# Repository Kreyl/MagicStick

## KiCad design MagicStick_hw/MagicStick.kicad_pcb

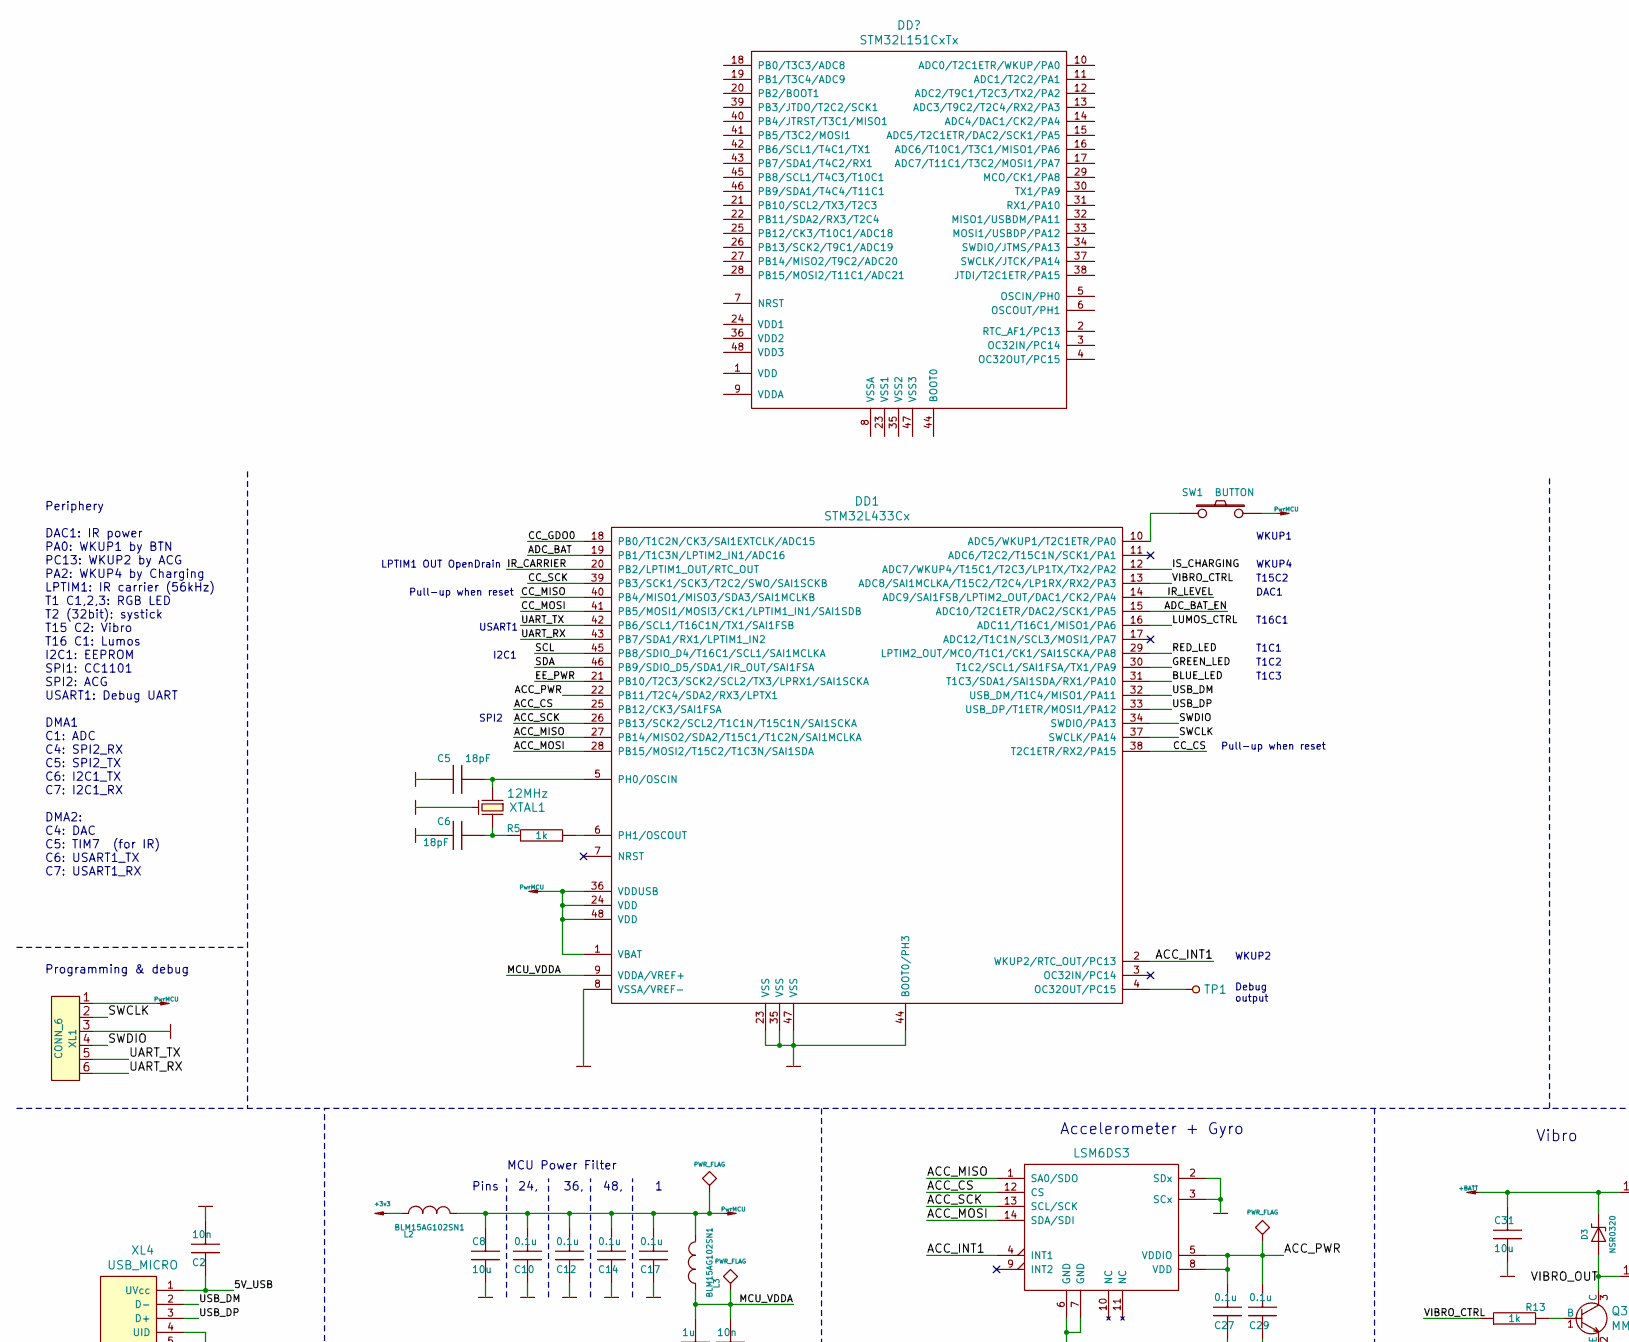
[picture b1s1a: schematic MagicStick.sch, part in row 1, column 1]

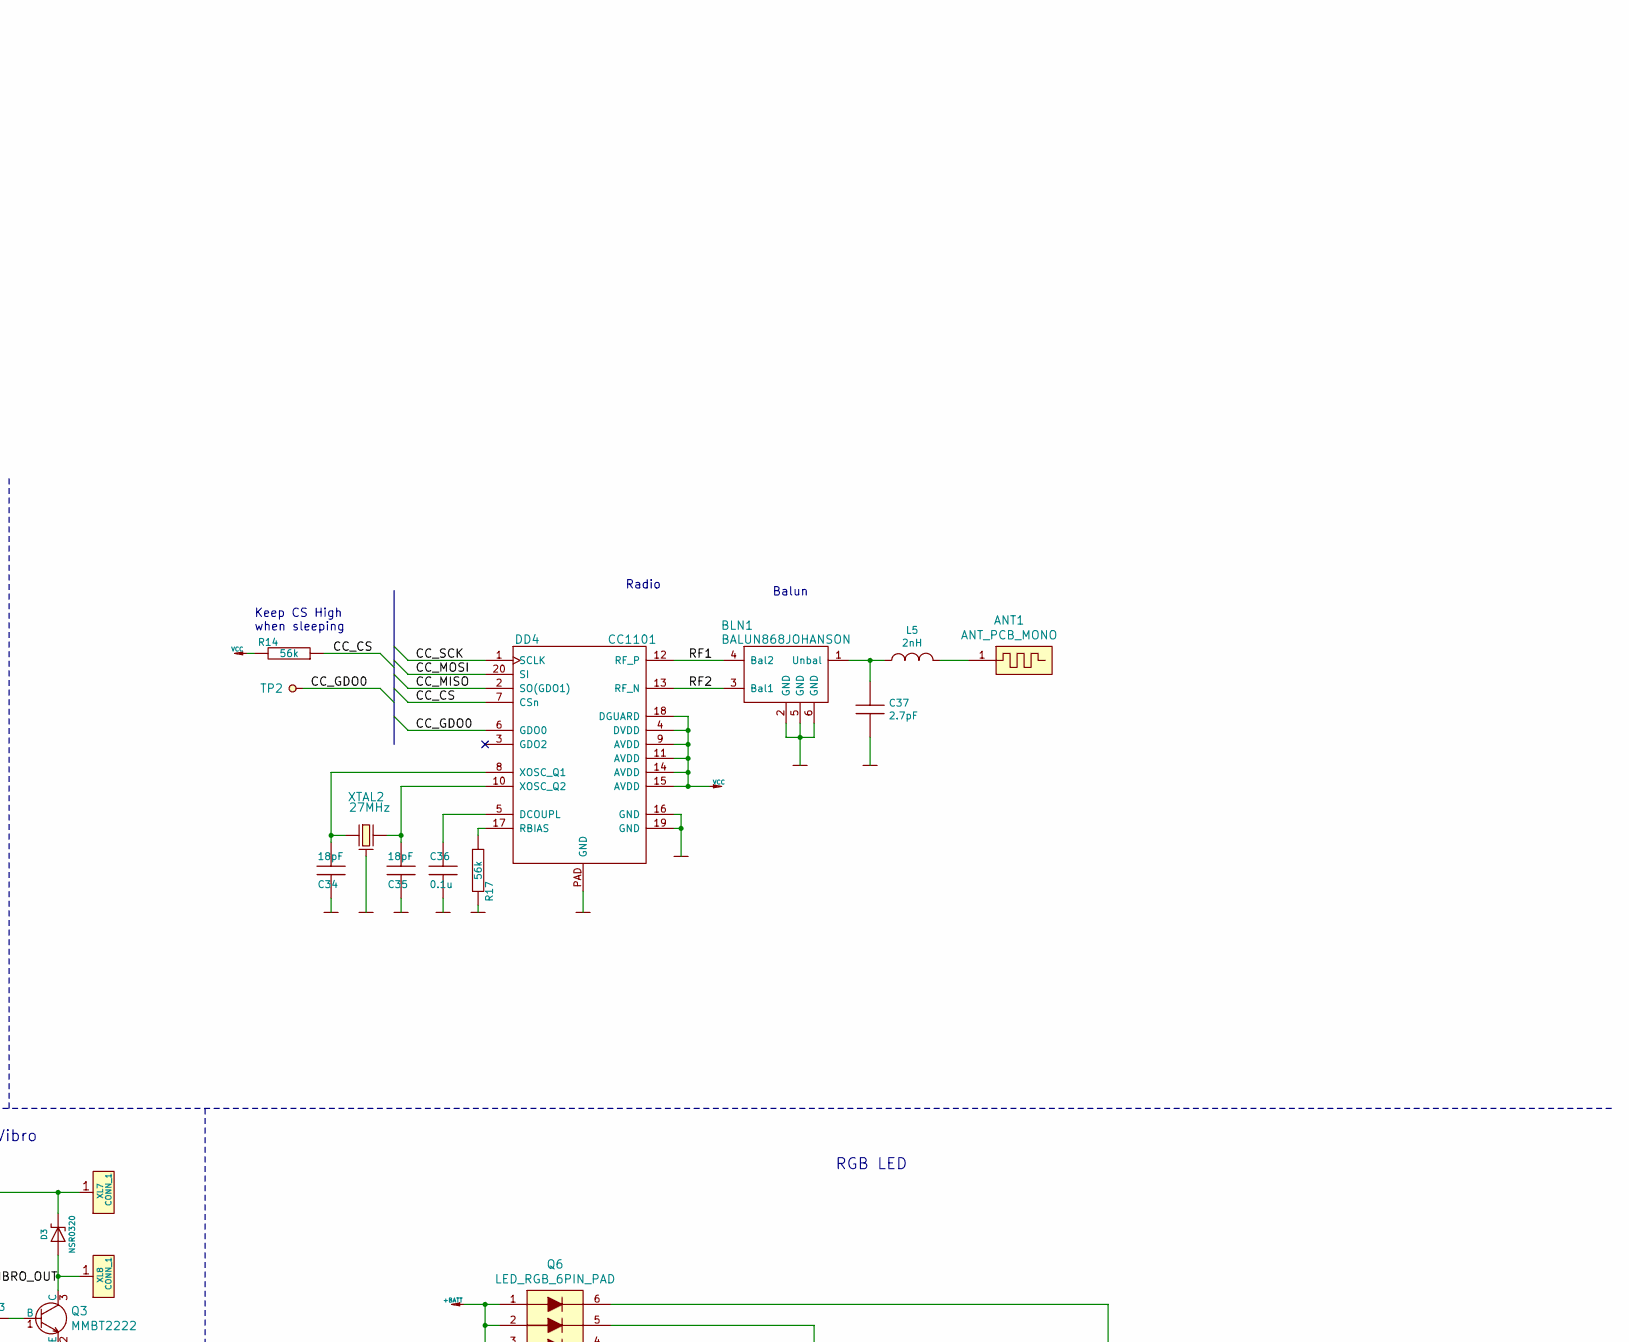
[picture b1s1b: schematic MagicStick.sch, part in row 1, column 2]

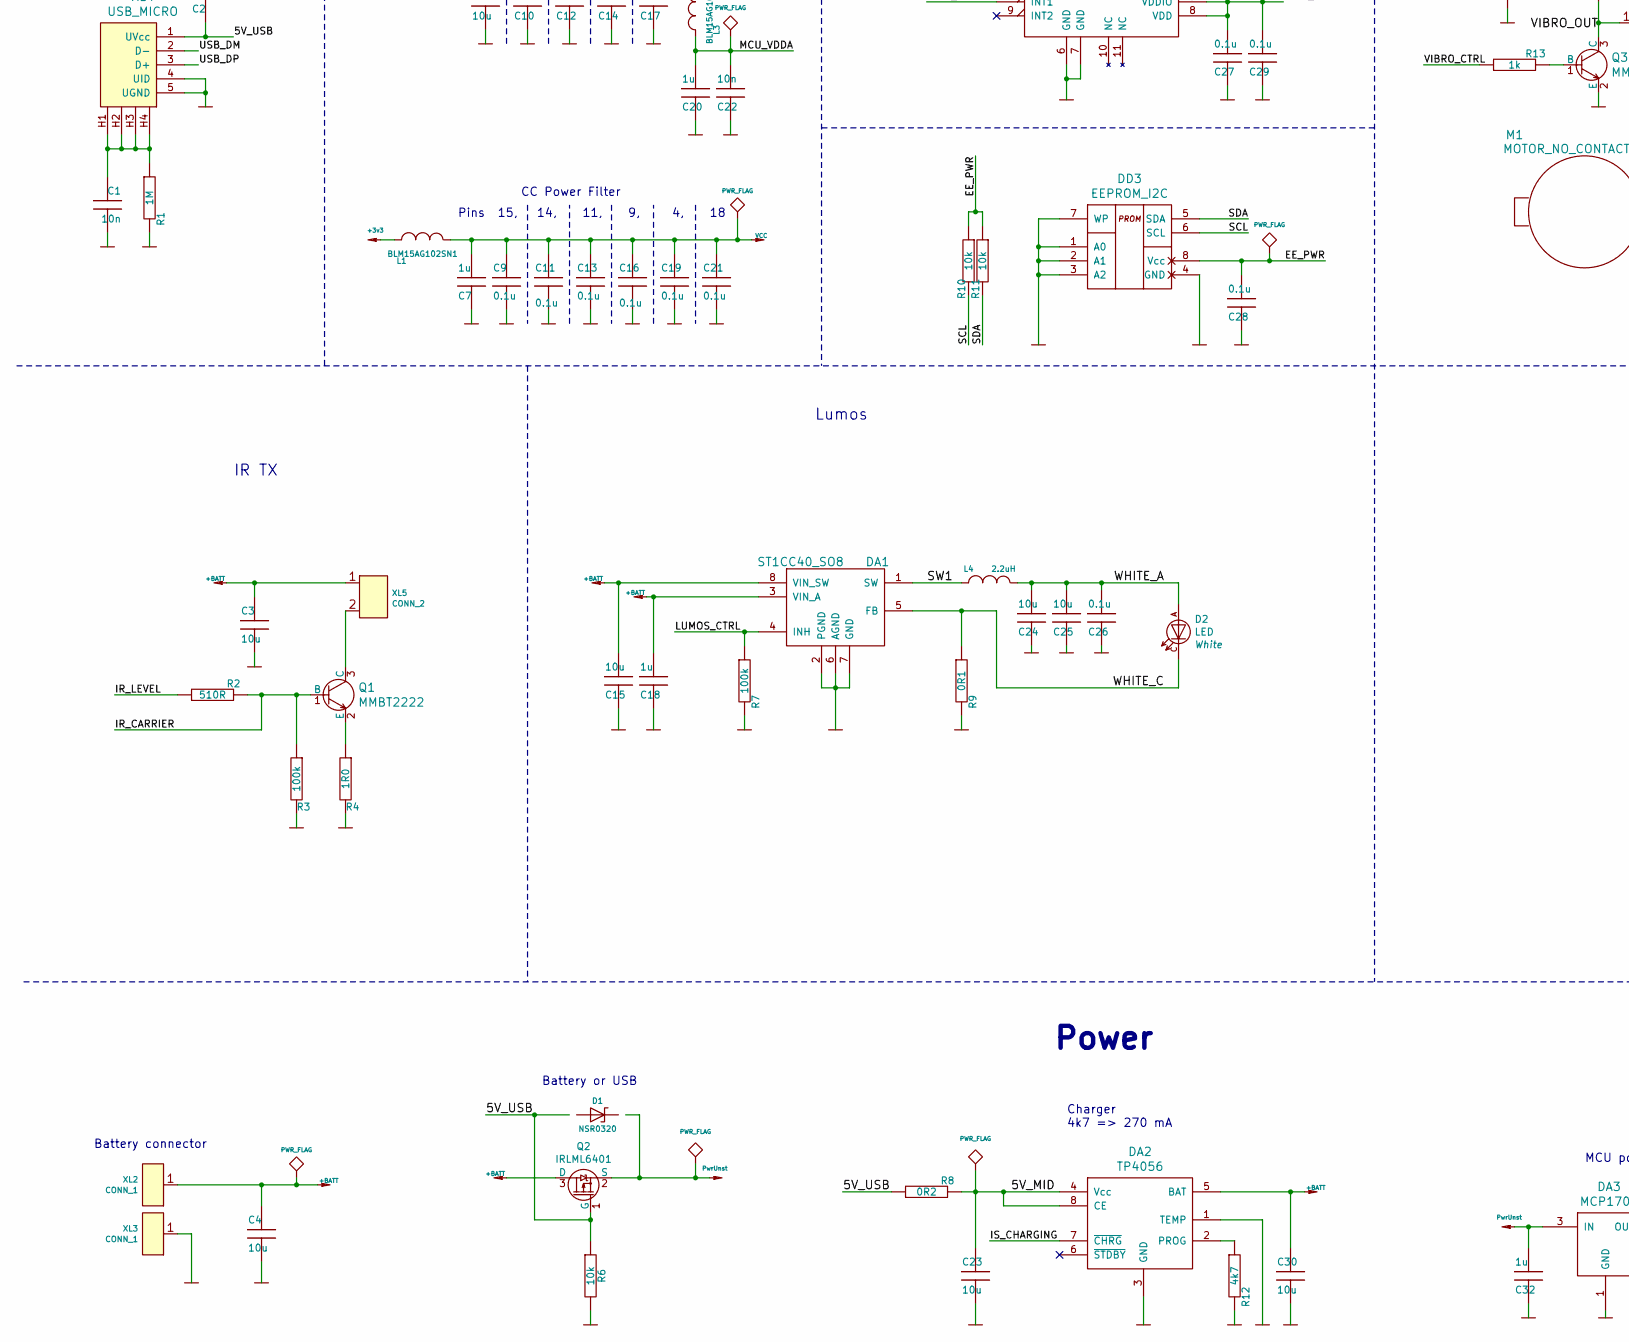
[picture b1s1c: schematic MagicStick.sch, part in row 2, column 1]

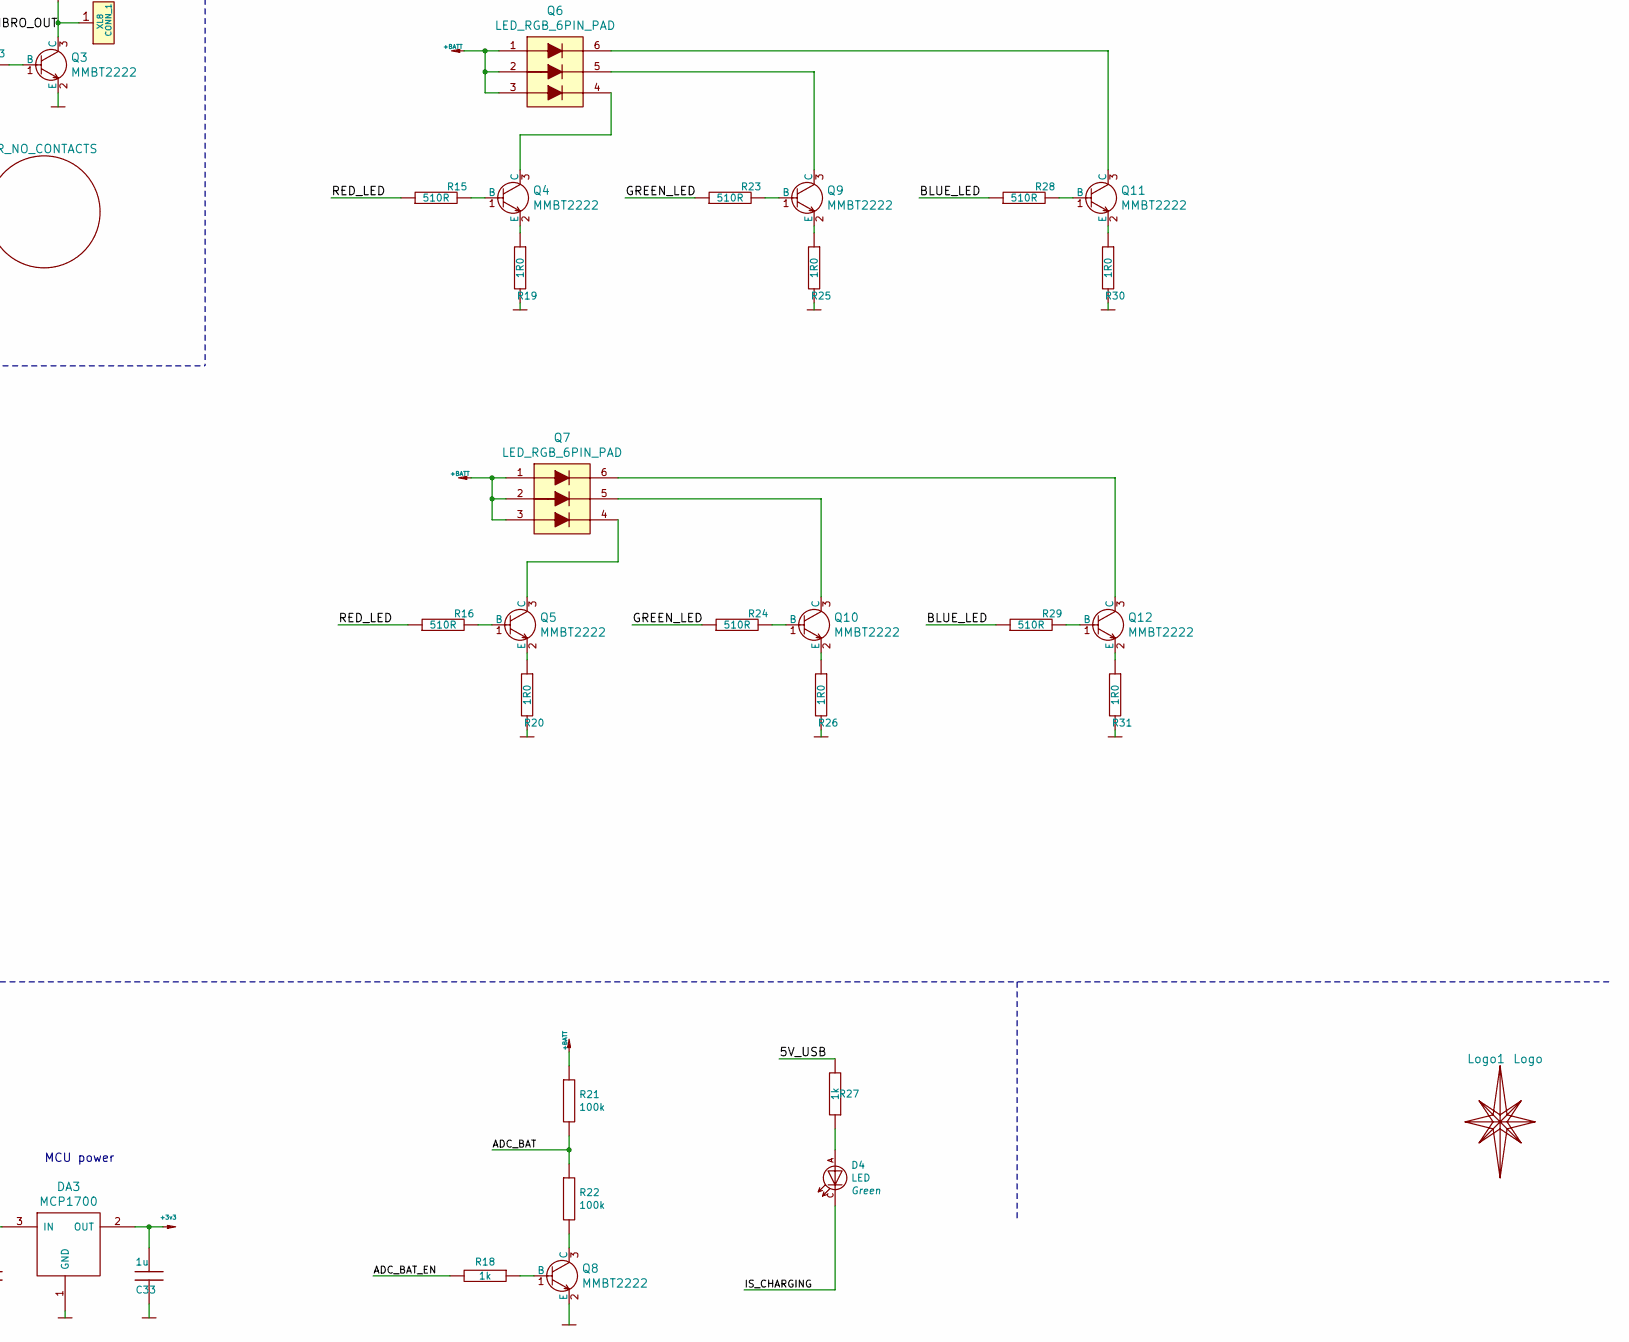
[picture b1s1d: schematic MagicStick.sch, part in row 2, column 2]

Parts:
ANT1: ANT_PCB_MONO; MagicStick
BLN1: BALUN868JOHANSON; BALUN_JOHANSON868
C1, C2, C22: 10n; CAP_0603
C3, C4, C8, C15, C23, C24, C25, C30, C31: 10u; CAP_0603
C5, C6, C34, C35: 18pF; CAP_0603
C7, C18, C20, C32, C33: 1u; CAP_0603
C9, C10, C11, C12, C13, C14, C16, C17, C19, C21, C26, C27, C28, C29, C36: 0.1u; CAP_0603
C37: 2.7pF; CAP_0402
D1, D3: NSR0320; SOD323
D2: LED; Cree_J3030
D4: LED; LED_0603
DA1: ST1CC40_SO8; SO8_150MIL
DA2: TP4056; SO8_150MIL
DA3: MCP1700; SOT23-3A
DD1: STM32L433Cx; LQFP48
DD2: LSM6DS3; 14_3x2d5_p0d5
DD3: EEPROM_I2C; SO8_150MIL
DD4: CC1101; QFN20
L1, L2, L3: BLM15AG102SN1; IND_0402
L4: 2.2uH; IND_SRN2512
L5: 2nH; IND_0402
Logo1: Logo; Ostranna_8x8
M1: MOTOR_NO_CONTACTS; Motor_no_Contacts
Q1, Q3, Q4, Q5, Q8, Q9, Q10, Q11, Q12: MMBT2222; SOT23-3
Q2: IRLML6401; SOT23-3
Q6, Q7: LED_RGB_6PIN_PAD; EpistarRGB
R1: 1M; RES_0603
R2, R15, R16, R23, R24, R28, R29: 510R; RES_0603
R3, R7, R21, R22: 100k; RES_0603
R4, R19, R20, R25, R26, R30, R31: 1R0; RES_0805
R5, R13, R18, R27: 1k; RES_0603
R6, R10, R11: 10k; RES_0603
R8: 0R2; RES_1206
R9: 0R1; RES_1206
R12: 4k7; RES_0603
R14, R17: 56k; RES_0603
SW1: BUTTON; BTN_4x4_SMD
TP1, TP2: TESTPOINT; TESTPOINT_1MM
XL1: CONN_6; PLS-6-NoHole
XL2, XL3, XL7, XL8: CONN_1; Oval3x1.5
XL4: USB_MICRO; USBmicro_MOLEX_1050170001
XL5: CONN_2; PBS-2
XTAL1: 12MHz; 03225C4
XTAL2: 27MHz; 03225C4

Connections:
+3.3V: C33.1, DA3.2 (OUT), L1.2, L2.2
+BATT: C3.2, C4.2, C15.1, C18.1, C30.2, C31.2, D3.C, DA1.3 (VIN_A), DA1.8 (VIN_SW), DA2.5 (BAT), Q2.3 (D), Q6.1, Q6.2, Q6.3, Q7.1, Q7.2, Q7.3, R21.1, XL2.1, XL5.1, XL7.1
/5V_MID: C23.2, DA2.4 (Vcc), DA2.8 (CE), R8.2
/5V_USB: C2.2, D1.A, Q2.1 (G), R6.1, R8.1, R27.2, XL4.1 (UVcc)
/ACC_CS: DD1.25 (PB12/CK3/SAI1FSA), DD2.12 (CS)
/ACC_INT1: DD1.2 (WKUP2/RTC_OUT/PC13), DD2.4 (INT1)
/ACC_MISO: DD1.27 (PB14/MISO2/SDA2/T15C1/T1C2N/SAI1MCLKA), DD2.1 (SA0/SDO)
/ACC_MOSI: DD1.28 (PB15/MOSI2/T15C2/T1C3N/SAI1SDA), DD2.14 (SDA/SDI)
/ACC_PWR: C27.1, C29.1, DD1.22 (PB11/T2C4/SDA2/RX3/LPTX1), DD2.5 (VDDIO), DD2.8 (VDD)
/ACC_SCK: DD1.26 (PB13/SCK2/SCL2/T1C1N/T15C1N/SAI1SCKA), DD2.13 (SCL/SCK)
/ADC_BAT: DD1.19 (PB1/T1C3N/LPTIM2_IN1/ADC16), R21.2, R22.1
/ADC_BAT_EN: DD1.15 (ADC10/T2C1ETR/DAC2/SCK1/PA5), R18.2
/BLUE_LED: DD1.31 (T1C3/SDA1/SAI1SDA/RX1/PA10), R28.1, R29.1
/CC_CS: DD1.38 (T2C1ETR/RX2/PA15), DD4.7 (CSn), R14.1
/CC_GDO0: DD1.18 (PB0/T1C2N/CK3/SAI1EXTCLK/ADC15), DD4.6 (GDO0), TP2.1
/CC_MISO: DD1.40 (PB4/MISO1/MISO3/SDA3/SAI1MCLKB), DD4.2 (SO(GDO1))
/CC_MOSI: DD1.41 (PB5/MOSI1/MOSI3/CK1/LPTIM1_IN1/SAI1SDB), DD4.20 (SI)
/CC_SCK: DD1.39 (PB3/SCK1/SCK3/T2C2/SWO/SAI1SCKB), DD4.1 (SCLK)
/EE_PWR: C28.1, DD1.21 (PB10/T2C3/SCK2/SCL2/TX3/LPRX1/SAI1SCKA), DD3.8 (Vcc), R10.1, R11.1
/GREEN_LED: DD1.30 (T1C2/SCL1/SAI1FSA/TX1/PA9), R23.1, R24.1
/IR_CARRIER: DD1.20 (PB2/LPTIM1_OUT/RTC_OUT), Q1.1 (B), R2.2, R3.1
/IR_LEVEL: DD1.14 (ADC9/SAI1FSB/LPTIM2_OUT/DAC1/CK2/PA4), R2.1
/IS_CHARGING: D4.C, DA2.7 (~CHRG), DD1.12 (ADC7/WKUP4/T15C1/T2C3/LP1TX/TX2/PA2)
/LUMOS_CTRL: DA1.4 (INH), DD1.16 (ADC11/T16C1/MISO1/PA6), R7.1
/MCU_VDDA: C20.1, C22.1, DD1.9 (VDDA/VREF+), L3.2
/RED_LED: DD1.29 (LPTIM2_OUT/MCO/T1C1/CK1/SAI1SCKA/PA8), R15.1, R16.1
/RF1: BLN1.4 (Bal2), DD4.12 (RF_P)
/RF2: BLN1.3 (Bal1), DD4.13 (RF_N)
/SCL: DD1.45 (PB8/SDIO_D4/T16C1/SCL1/SAI1MCLKA), DD3.6 (SCL), R10.2
/SDA: DD1.46 (PB9/SDIO_D5/SDA1/IR_OUT/SAI1FSA), DD3.5 (SDA), R11.2
/SW1: DA1.1 (SW), L4.2
/SWCLK: DD1.37 (SWCLK/PA14), XL1.2
/SWDIO: DD1.34 (SWDIO/PA13), XL1.4
/UART_RX: DD1.43 (PB7/SDA1/RX1/LPTIM1_IN2), XL1.6
/UART_TX: DD1.42 (PB6/SCL1/T16C1N/TX1/SAI1FSB), XL1.5
/USB_DM: DD1.32 (USB_DM/T1C4/MISO1/PA11), XL4.2 (D-)
/USB_DP: DD1.33 (USB_DP/T1ETR/MOSI1/PA12), XL4.3 (D+)
/VIBRO_CTRL: DD1.13 (ADC8/SAI1MCLKA/T15C2/T2C4/LP1RX/RX2/PA3), R13.1
/VIBRO_OUT: D3.A, Q3.3 (C), XL8.1
/WHITE_A: C24.1, C25.1, C26.1, D2.A, L4.1
/WHITE_C: D2.C, DA1.5 (FB), R9.1
GND: BLN1.2 (GND), BLN1.5 (GND), BLN1.6 (GND), C1.1, C2.1, C3.1, C4.1, C5.2, C6.2, C7.2, C8.1, C9.2, C10.2, C11.2, C12.2, C13.2, C14.2, C15.2, C16.2, C17.2, C18.2, C19.2, C20.2, C21.2, C22.2, C23.1, C24.2, C25.2, C26.2, C27.2, C28.2, C29.2, C30.1, C31.1, C32.2, C33.2, C34.2, C35.2, C36.1, C37.2, DA1.2 (PGND), DA1.6 (AGND), DA1.7 (GND), DA2.1 (TEMP), DA2.3 (GND), DA3.1 (GND), DD1.8 (VSSA/VREF-), DD1.23 (VSS), DD1.35 (VSS), DD1.44 (BOOT0/PH3), DD1.47 (VSS), DD2.2 (SDx), DD2.3 (SCx), DD2.6 (GND), DD2.7 (GND), DD3.1 (A0), DD3.2 (A1), DD3.3 (A2), DD3.4 (GND), DD3.7 (WP), DD4.16 (GND), DD4.19 (GND), DD4.PAD (GND), Q3.2 (E), Q8.2 (E), R1.2, R3.2, R4.2, R6.2, R7.2, R9.2, R12.2, R17.2, R19.2, R20.2, R25.2, R26.2, R30.2, R31.2, XL1.3, XL3.1, XL4.4 (UID), XL4.5 (UGND), XTAL1.H, XTAL2.H; also elsewhere on the board
unnamed 42: ANT1.1, L5.2; also elsewhere on the board
unnamed: BLN1.1 (Unbal), C37.1, L5.1
unnamed: C1.2, R1.1, XL4.H1, XL4.H2, XL4.H3, XL4.H4
unnamed: C5.1, DD1.5 (PH0/OSCIN), XTAL1.1
unnamed: C6.1, R5.2, XTAL1.2
unnamed: C34.1, DD4.8 (XOSC_Q1), XTAL2.1
unnamed: C35.1, DD4.10 (XOSC_Q2), XTAL2.2
unnamed: C36.2, DD4.5 (DCOUPL)
unnamed: D4.A, R27.1
unnamed: DA2.2 (PROG), R12.1
unnamed: DD1.4 (OC32OUT/PC15), TP1.1
unnamed: DD1.6 (PH1/OSCOUT), R5.1
unnamed: DD1.10 (ADC5/WKUP1/T2C1ETR/PA0), SW1.1
unnamed: DD4.17 (RBIAS), R17.1
unnamed: Q1.2 (E), R4.1
unnamed: Q1.3 (C), XL5.2 (PM)
unnamed: Q3.1 (B), R13.2
unnamed: Q4.1 (B), R15.2
unnamed: Q4.2 (E), R19.1
unnamed: Q4.3 (C), Q6.4 (B)
unnamed: Q5.1 (B), R16.2
unnamed: Q5.2 (E), R20.1
unnamed: Q5.3 (C), Q7.4 (B)
unnamed: Q6.5 (G), Q9.3 (C)
unnamed: Q8.1 (B), R18.1
unnamed: Q8.3 (C), R22.2
unnamed: Q9.1 (B), R23.2
unnamed: Q9.2 (E), R25.1
unnamed: Q10.1 (B), R24.2
unnamed: Q10.2 (E), R26.1
unnamed: Q7.5 (G), Q10.3 (C)
unnamed: Q11.1 (B), R28.2
unnamed: Q11.2 (E), R30.1
unnamed: Q6.6, Q11.3 (C)
unnamed: Q12.1 (B), R29.2
unnamed: Q12.2 (E), R31.1
unnamed: Q7.6, Q12.3 (C)
PwrMCU: C8.2, C10.1, C12.1, C14.1, C17.1, DD1.1 (VBAT), DD1.24 (VDD), DD1.36 (VDDUSB), DD1.48 (VDD), L2.1, L3.1, SW1.2, XL1.1
PwrUnst: C32.1, D1.C, DA3.3 (IN), Q2.2 (S)
VCC: C7.1, C9.1, C11.1, C13.1, C16.1, C19.1, C21.1, DD4.4 (DVDD), DD4.9 (AVDD), DD4.11 (AVDD), DD4.14 (AVDD), DD4.15 (AVDD), DD4.18 (DGUARD), L1.1, R14.2

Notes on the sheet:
RGB LED
MCU Power Filter
Pins 24, 36, 48, 1
CC Power Filter
Pins 15, 14, 11, 9, 4, 18
Periphery DAC1: IR power PA0: WKUP1 by BTN PC13: WKUP2 by ACG PA2: WKUP4 by Charging LPTIM1: IR carrier (56kHz) T1 C1,2,3: RGB LED T2 (32bit): systick T15 C2: Vibro T16 C1: Lumos I2C1: EEPROM SPI1: CC1101 SPI2: ACG USART1: Debug UART DMA1 C1: ADC C4: SPI2_RX C5: SPI2_TX C6: I2C1_TX C7: I2C1_RX DMA2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
Programming & debug
Radio
Balun
Keep CS High when sleeping
Accelerometer + Gyro
MCU power
Power
Charger 4k7 => 270 mA
Battery or USB
Battery connector
Vibro
WKUP2
T1C1
T1C2
T1C3
I2C1
SPI2
LPTIM1 OUT OpenDrain
Pull-up when reset
Debug output
USART1
IR TX
Lumos
T16C1
T15C2
DAC1
WKUP1
WKUP4

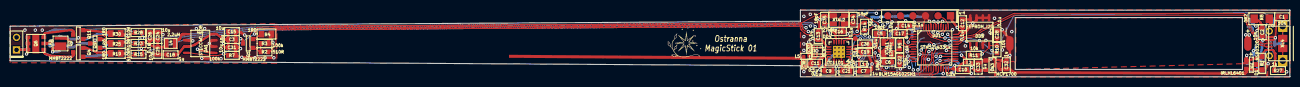
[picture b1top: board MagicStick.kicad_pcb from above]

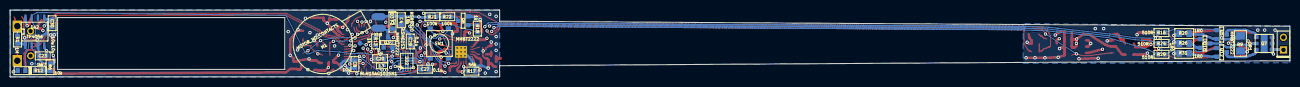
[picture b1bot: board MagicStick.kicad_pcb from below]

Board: 4 copper layers, 259.1 x 13.5 mm, 113 parts (38 on the bottom side), 82 nets.

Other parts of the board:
C38: *; CAP_0402

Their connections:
GND: C38.2; also elsewhere on the board
unnamed 42: C38.1; also elsewhere on the board

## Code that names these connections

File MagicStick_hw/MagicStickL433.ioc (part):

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Mcu.Name=STM32L433C(B-C)Tx
Mcu.Package=LQFP48
Mcu.UserName=STM32L433CBTx
PA0.Mode=SYS_WakeUp0
PA0.Signal=SYS_WKUP1
PA1.Mode=PWM Generation1 CH1N
PA1.Signal=TIM15_CH1N
PA10.Signal=S_TIM1_CH3
PA11.Mode=Device
PA11.Signal=USB_DM
PA12.Mode=Device
PA12.Signal=USB_DP
PA13\ (JTMS-SWDIO).Mode=Serial_Wire
PA13\ (JTMS-SWDIO).Signal=SYS_JTMS-SWDIO
PA14\ (JTCK-SWCLK).Mode=Serial_Wire
PA14\ (JTCK-SWCLK).Signal=SYS_JTCK-SWCLK
PA15\ (JTDI).Signal=GPIO_Output
PA2.Mode=SYS_WakeUp3
PA2.Signal=SYS_WKUP4
PA3.Signal=S_TIM15_CH2
PA4.Signal=COMP_DAC11_group
PA5.Signal=GPIO_Output
PA6.Signal=S_TIM16_CH1
PA8.Signal=S_TIM1_CH1
PA9.Signal=S_TIM1_CH2
PB0.Signal=GPIO_Input
PB1.Signal=ADCx_IN16
PB10.Signal=GPIO_Output
PB11.Signal=GPIO_Output
PB12.Signal=GPIO_Output
PB13.Mode=Full_Duplex_Master
PB13.Signal=SPI2_SCK
PB14.Mode=Full_Duplex_Master
PB14.Signal=SPI2_MISO
PB15.Mode=Full_Duplex_Master
PB15.Signal=SPI2_MOSI
PB2.Mode=WaveformGeneration
PB2.Signal=LPTIM1_OUT
PB3\ (JTDO-TRACESWO).Mode=Full_Duplex_Master
PB3\ (JTDO-TRACESWO).Signal=SPI1_SCK
PB4\ (NJTRST).Mode=Full_Duplex_Master
PB4\ (NJTRST).Signal=SPI1_MISO
PB5.Mode=Full_Duplex_Master
PB5.Signal=SPI1_MOSI
PB6.Mode=Asynchronous
PB6.Signal=USART1_TX
PB7.Mode=Asynchronous
PB7.Signal=USART1_RX
PB8.Mode=I2C
PB8.Signal=I2C1_SCL
PB9.Mode=I2C
PB9.Signal=I2C1_SDA
PC13.Mode=SYS_WakeUp1
PC13.Signal=SYS_WKUP2
PC15-OSC32_OUT\ (PC15).Signal=GPIO_Output
PH0-OSC_IN\ (PH0).Mode=HSE-External-Oscillator
PH0-OSC_IN\ (PH0).Signal=RCC_OSC_IN
PH1-OSC_OUT\ (PH1).Mode=HSE-External-Oscillator
PH1-OSC_OUT\ (PH1).Signal=RCC_OSC_OUT
RCC.HSE_VALUE=12000000
RCC.SYSCLKFreq_VALUE=16000000
RCC.SYSCLKSource=RCC_SYSCLKSOURCE_PLLCLK
board=custom

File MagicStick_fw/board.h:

#pragma once

// ==== General ====
#define APP_NAME            "MagicStick"

// Version of PCB
#define PCB_VER                 1

// MCU type as defined in the ST header.
#define STM32L433xx

// Freq of external crystal if any. Leave it here even if not used.
#define CRYSTAL_FREQ_HZ         12000000

// OS timer settings
#define STM32_ST_IRQ_PRIORITY   2
#define STM32_ST_USE_TIMER      2
#define SYS_TIM_CLK             (Clk.APB1FreqHz)    // Timer 5 is clocked by APB1

//  Periphery
#define I2C1_ENABLED            TRUE
#define I2C2_ENABLED            FALSE
#define I2C3_ENABLED            FALSE
#define SIMPLESENSORS_ENABLED   TRUE
#define BUTTONS_ENABLED         TRUE

#define ADC_REQUIRED            FALSE
#define STM32_DMA_REQUIRED      TRUE    // Leave this macro name for OS

#if 1 // ========================== GPIO =======================================
// EXTI
#define INDIVIDUAL_EXTI_IRQ_REQUIRED    FALSE

// Buttons
#define BTN1_PIN        GPIOA, 0

// Vibro
#define VIBRO_CTRL      { GPIOA, 3, TIM15, 2, invNotInverted, omPushPull, 99 }

// IR TX
#define IR_LVL_PIN      GPIOA, 4
#define IR_CARRIER_PIN  GPIOB, 2

// Battery
#define IS_CHARGING     GPIOA, 2, pudPullUp
#define BAT_MEAS_EN     GPIOA, 5
#define BAT_ADC_PIN     GPIOB, 1

// Light
#define LUMOS_CTRL      { GPIOA, 6, TIM16, 1, invNotInverted, omPushPull, 255 }
#define LED_B_PIN       { GPIOA, 8, TIM1, 1, invNotInverted, omPushPull, 255 }
#define LED_R_PIN       { GPIOA, 9, TIM1, 2, invNotInverted, omPushPull, 255 }
#define LED_G_PIN       { GPIOA, 10, TIM1, 3, invNotInverted, omPushPull, 255 }

// USB
#define USB_DM          GPIOA, 11
#define USB_DP          GPIOA, 12
#define USB_AF          AF10
#define USB_DETECT_PIN  GPIOA, 7

// Radio: SPI, PGpio, Sck, Miso, Mosi, Cs, Gdo0
#define CC_Setup0       SPI1, GPIOB, 3,4,5, GPIOA,15, GPIOB,0

// UART
#define UART_GPIO       GPIOB
#define UART_TX_PIN     6
#define UART_RX_PIN     7

// Acc
#define ACG_IRQ_PIN     GPIOC, 13
#define ACG_CS_PIN      GPIOB, 12
#define ACG_SCK_PIN     GPIOB, 13, omPushPull, pudNone, AF5
#define ACG_MISO_PIN    GPIOB, 14, omPushPull, pudNone, AF5
#define ACG_MOSI_PIN    GPIOB, 15, omPushPull, pudNone, AF5
#define ACG_PWR_PIN     GPIOB, 11
#define ACG_SPI         SPI2

// I2C
#define I2C1_GPIO       GPIOB
#define I2C1_SCL        8
#define I2C1_SDA        9
// I2C Alternate Function
#define I2C_AF          AF4

#define EE_PWR_PIN      GPIOB, 10

#endif // GPIO

#if 1 // ============================== Timer ==================================
#define IR_SAMPLING_TMR TIM7
#endif

#if 1 // =========================== I2C =======================================
// i2cclkPCLK1, i2cclkSYSCLK, i2cclkHSI
#define I2C_CLK_SRC     i2cclkHSI
#define I2C_BAUDRATE_HZ 400000
#endif

#if ADC_REQUIRED // ======================= Inner ADC ==========================
// Clock divider: clock is generated from the APB2
#define ADC_CLK_DIVIDER		adcDiv2

// ADC channels
#define ADC_BATTERY_CHNL 	14
// ADC_VREFINT_CHNL
#define ADC_CHANNELS        { ADC_BATTERY_CHNL, ADC_VREFINT_CHNL }
#define ADC_CHANNEL_CNT     2   // Do not use countof(AdcChannels) as preprocessor does not know what is countof => cannot check
#define ADC_SAMPLE_TIME     ast24d5Cycles
#define ADC_OVERSAMPLING_RATIO  64   // 1 (no oversampling), 2, 4, 8, 16, 32, 64, 128, 256
#endif

#if 1 // =========================== DMA =======================================
// ==== Uart ====
// Remap is made automatically if required
#define UART_DMA_TX     STM32_DMA_STREAM_ID(2, 6)
#define UART_DMA_RX     STM32_DMA_STREAM_ID(2, 7)
#define UART_DMA_CHNL   2
#define UART_DMA_TX_MODE(Chnl) (STM32_DMA_CR_CHSEL(Chnl) | DMA_PRIORITY_LOW | STM32_DMA_CR_MSIZE_BYTE | STM32_DMA_CR_PSIZE_BYTE | STM32_DMA_CR_MINC | STM32_DMA_CR_DIR_M2P | STM32_DMA_CR_TCIE)
#define UART_DMA_RX_MODE(Chnl) (STM32_DMA_CR_CHSEL(Chnl) | DMA_PRIORITY_MEDIUM | STM32_DMA_CR_MSIZE_BYTE | STM32_DMA_CR_PSIZE_BYTE | STM32_DMA_CR_MINC | STM32_DMA_CR_DIR_P2M | STM32_DMA_CR_CIRC)

// ==== ACG ====
#define ACG_DMA_TX      STM32_DMA_STREAM_ID(1, 5)
#define ACG_DMA_RX      STM32_DMA_STREAM_ID(1, 4)
#define ACG_DMA_CHNL    1

// ==== I2C ====
#define I2C1_DMA_TX     STM32_DMA_STREAM_ID(1, 6)
#define I2C1_DMA_RX     STM32_DMA_STREAM_ID(1, 7)
#define I2C1_DMA_CHNL   3

#define DAC_DMA         STM32_DMA_STREAM_ID(2, 4)
#define DAC_DMA_CHNL    3

#if ADC_REQUIRED
#define ADC_DMA         STM32_DMA1_STREAM1
#define ADC_DMA_MODE    STM32_DMA_CR_CHSEL(0) |   /* DMA1 Stream1 Channel0 */ \
                        DMA_PRIORITY_LOW | \
                        STM32_DMA_CR_MSIZE_HWORD | \
                        STM32_DMA_CR_PSIZE_HWORD | \
                        STM32_DMA_CR_MINC |       /* Memory pointer increase */ \
                        STM32_DMA_CR_DIR_P2M |    /* Direction is peripheral to memory */ \
                        STM32_DMA_CR_TCIE         /* Enable Transmission Complete IRQ */
#endif // ADC

#endif // DMA

#if 1 // ========================== USART ======================================
#define PRINTF_FLOAT_EN FALSE
#define UART_TXBUF_SZ   8192
#define UART_RXBUF_SZ   99

#define UARTS_CNT       1

#define CMD_UART_PARAMS \
    USART1, UART_GPIO, UART_TX_PIN, UART_GPIO, UART_RX_PIN, \
    UART_DMA_TX, UART_DMA_RX, UART_DMA_TX_MODE(UART_DMA_CHNL), UART_DMA_RX_MODE(UART_DMA_CHNL), \
    true // Use independent clock

#endif

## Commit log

2018-12-28 Sch started
2018-12-28 proceeding
2019-01-16 + Stick PCB layout done
2019-01-18 Minor
2019-01-19 Ready for factory
2019-02-02 Uart works
2019-02-02 Uart RX ok
2019-02-02 + Acg works
2019-02-02 + LEDs ok + CC init ok
2019-02-02 + Btn + Vibro
2019-02-02 + Antenna matched
2019-02-04 + i2c
2019-02-12 no message
2019-02-22 StateMachine Diagrams added
2019-02-24 Duel is done
2019-03-03 + L151 code
2019-03-03 + Lumos On/Off
2019-03-03 Lumos done Sleep done
2019-03-04 + L151 Avada code * CC TX race condition fixed
2019-03-31 Working on transmitter
2019-06-02 + L151 Lumos code
2020-01-24 * Acc: 16g * 104 Hz
